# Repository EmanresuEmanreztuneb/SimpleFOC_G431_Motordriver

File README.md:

# SimpleFOC_G431_Motordriver (24V version)
A motordriver based in STM's G431 Drone ESC

Reason to create it was mainly because of the poor thermal performance of the original development board.
Now the whole "layer sandwich" is gone and every existing active layer can breath fresh air.

Changes:

<ins>**Two layer**</ins> <br>
&nbsp;&nbsp;&nbsp;&nbsp;&nbsp;&nbsp;&nbsp;&nbsp;As mentioned, the layer count has been reduced from eight to just two.<br>
&nbsp;&nbsp;&nbsp;&nbsp;&nbsp;&nbsp;&nbsp;&nbsp;The KiCad files still include two "blind" internal layers between top<br>
&nbsp;&nbsp;&nbsp;&nbsp;&nbsp;&nbsp;&nbsp;&nbsp;and bottom to test whether additional shielding makes a difference.<br>
&nbsp;&nbsp;&nbsp;&nbsp;&nbsp;&nbsp;&nbsp;&nbsp;to test if the additional shielding makes any difference.<br>
&nbsp;&nbsp;&nbsp;&nbsp;&nbsp;&nbsp;&nbsp;&nbsp;Spoiler: It doesn’t...<br>
&nbsp;&nbsp;&nbsp;&nbsp;&nbsp;&nbsp;&nbsp;&nbsp;You can remove these layers if you plan to etch the PCB at home.<br> 
&nbsp;&nbsp;&nbsp;&nbsp;&nbsp;&nbsp;&nbsp;&nbsp;However, since the price at JLC remains nearly the same, I left them in.<br>
&nbsp;&nbsp;&nbsp;&nbsp;&nbsp;&nbsp;&nbsp;&nbsp;Adding them later would be more effort than simply removing them now.<br>

<ins>**Pins**</ins> <br>
&nbsp;&nbsp;&nbsp;&nbsp;&nbsp;&nbsp;&nbsp;&nbsp;To maintain the required dimensions while sticking to a two-layer design,<br>
&nbsp;&nbsp;&nbsp;&nbsp;&nbsp;&nbsp;&nbsp;&nbsp;I unfortunately had to remove the thermal sensor and LEDs.<br>
&nbsp;&nbsp;&nbsp;&nbsp;&nbsp;&nbsp;&nbsp;&nbsp;But you get new pins for your own modifications. (PA15, C10, C11, B5)<br>

<ins>**Stable 24V**</ins> <br>
&nbsp;&nbsp;&nbsp;&nbsp;&nbsp;&nbsp;&nbsp;&nbsp;On the original version, 24V operation was borderline and carried a high<br>
&nbsp;&nbsp;&nbsp;&nbsp;&nbsp;&nbsp;&nbsp;&nbsp;risk of component failure.<br>
&nbsp;&nbsp;&nbsp;&nbsp;&nbsp;&nbsp;&nbsp;&nbsp;The current design uses the LMR23630 for the first stage (VCC to 10V),<br>
&nbsp;&nbsp;&nbsp;&nbsp;&nbsp;&nbsp;&nbsp;&nbsp;which safely handles up to 36V.<br>
&nbsp;&nbsp;&nbsp;&nbsp;&nbsp;&nbsp;&nbsp;&nbsp;A 60V version is also planned; this will require upgrading to an LMR51635<br>
&nbsp;&nbsp;&nbsp;&nbsp;&nbsp;&nbsp;&nbsp;&nbsp;and adjusting the VCC sense resistors.<br>

<ins>**BOOT / Encoder**</ins> <br>
&nbsp;&nbsp;&nbsp;&nbsp;&nbsp;&nbsp;&nbsp;&nbsp;In the previous version, the BOOT pin (PB8) was used for Encoder Z with a<br>
&nbsp;&nbsp;&nbsp;&nbsp;&nbsp;&nbsp;&nbsp;&nbsp;pull-up and capacitor. This could cause startup issues, as the system <br>
&nbsp;&nbsp;&nbsp;&nbsp;&nbsp;&nbsp;&nbsp;&nbsp;relies on the capacitor's charging time to keep PB8 low during boot.<br>

&nbsp;&nbsp;&nbsp;&nbsp;&nbsp;&nbsp;&nbsp;&nbsp;The new design uses pull-downs without capacitors. This drops support for <br>
&nbsp;&nbsp;&nbsp;&nbsp;&nbsp;&nbsp;&nbsp;&nbsp;open-collector encoders, but standard models (AMS, CUI, MT6835, MT6701) <br>
&nbsp;&nbsp;&nbsp;&nbsp;&nbsp;&nbsp;&nbsp;&nbsp;work flawlessly.<br>

<ins>**ToDo**</ins> <br>
&nbsp;&nbsp;&nbsp;&nbsp;&nbsp;&nbsp;&nbsp;&nbsp;Current-sense gain requires a surprisingly high value to match real-world<br>
&nbsp;&nbsp;&nbsp;&nbsp;&nbsp;&nbsp;&nbsp;&nbsp;measurements. ->>> Investigating the root cause.<br>

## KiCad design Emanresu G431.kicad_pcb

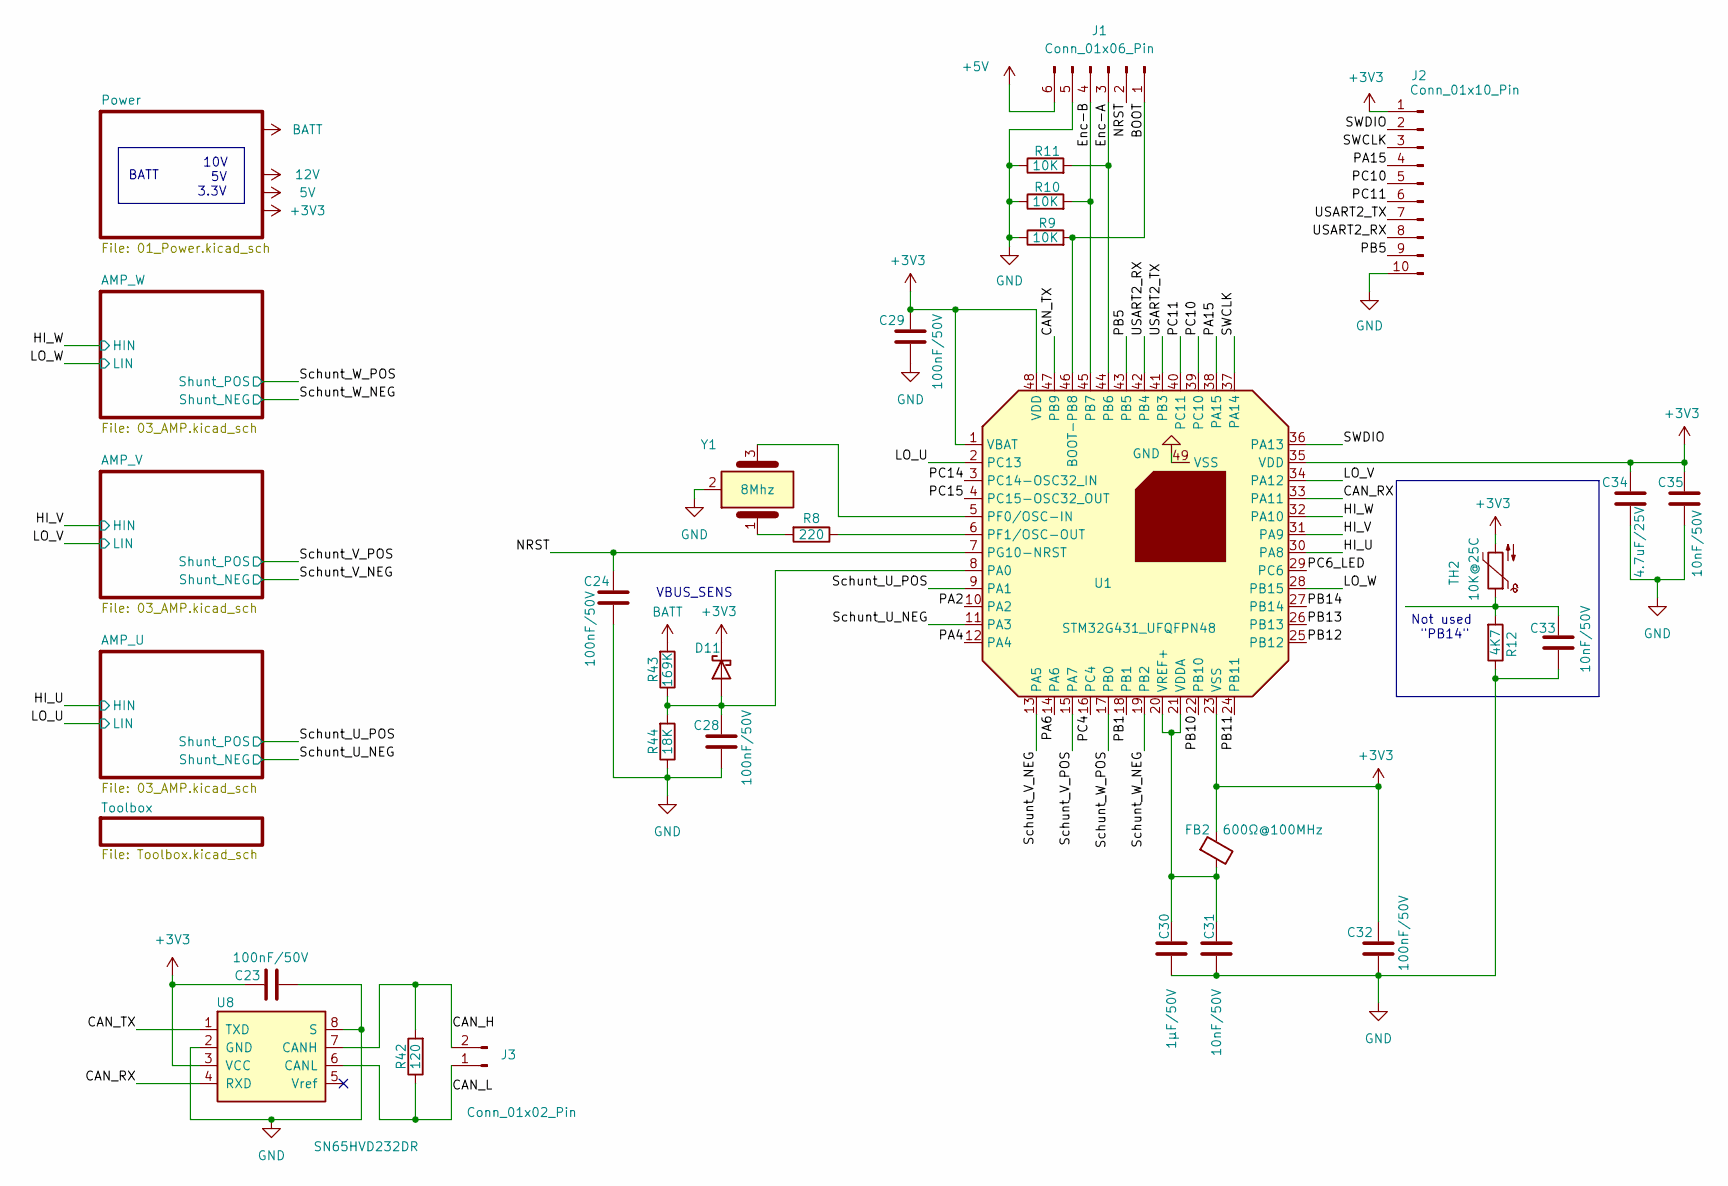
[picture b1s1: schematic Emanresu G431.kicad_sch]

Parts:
C23, C24, C28, C29, C32: 100nF/50V; C_0603_1608Metric; LCSC C14663
C30: 1μF/50V; C_0603_1608Metric; LCSC C15849
C31, C33, C35: 10nF/50V; C_0603_1608Metric; LCSC C100042
C34: 4.7uF/25V; C_0603_1608Metric; LCSC C69335
D11: D_Schottky; D_SOD-523; LCSC C2926449
FB2: 600Ω@100MHz; R_0603_1608Metric; LCSC C1002
J1: Conn_01x06_Pin; PinHeader_2x03_P2.54mm_Vertical
J2: Conn_01x10_Pin; PinHeader_1x10_P2.54mm_Vertical
J3: Conn_01x02_Pin; PinHeader_1x02_P2.54mm_Vertical
R8: 220; R_0603_1608Metric; LCSC C22962
R9, R10, R11: 10K; R_0603_1608Metric; LCSC C25804
R12: 4K7; R_0603_1608Metric; JLCPCB C23162
R42: 120; R_0603_1608Metric; LCSC C22787
R43: 169K; R_0603_1608Metric; LCSC C22817
R44: 18K; R_0603_1608Metric; LCSC C25810
TH2: 10K@25C; R_0603_1608Metric; JLCPCB C13564
U1: STM32G431_UFQFPN48; STM32 G431 QFN-48-1EP_7x7mm; LCSC C529356
U8: SN65HVD232DR; SOIC-8_3.9x4.9mm_P1.27mm; LCSC C30530
Y1: 8Mhz; CSTNE8M00GH5C000R0; LCSC C341525

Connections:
+3V3: C23.2, C29.2, C32.2, C34.2, C35.2, D11.1 (K), FB2.1, J2.1, TH2.2, U1.1 (VBAT), U1.23 (VSS), U1.35 (VDD), U1.48 (VDD), U8.3 (VCC); also elsewhere on the board
+5V: J1.6; also elsewhere on the board
/BOOT: J1.1, R9.2, U1.46 (BOOT-PB8)
/CAN_H: J3.2, R42.2, U8.7 (CANH)
/CAN_L: J3.1, R42.1, U8.6 (CANL)
/CAN_RX: U1.33 (PA11), U8.4 (RXD)
/CAN_TX: U1.47 (PB9), U8.1 (TXD)
/Enc-A: J1.3, R11.2, U1.44 (PB6)
/Enc-B: J1.4, R10.2, U1.45 (PB7)
/HI_U: U1.30 (PA8); also elsewhere on the board
/HI_V: U1.31 (PA9); also elsewhere on the board
/HI_W: U1.32 (PA10); also elsewhere on the board
/LO_U: U1.2 (PC13); also elsewhere on the board
/LO_V: U1.34 (PA12); also elsewhere on the board
/LO_W: U1.28 (PB15); also elsewhere on the board
/NRST: C24.2, J1.2, U1.7 (PG10-NRST)
/PA2: U1.10 (PA2)
/PA4: U1.12 (PA4)
/PA6: U1.14 (PA6)
/PA15: J2.4, U1.38 (PA15)
/PB1: U1.18 (PB1)
/PB5: J2.9, U1.43 (PB5)
/PB10: U1.22 (PB10)
/PB11: U1.24 (PB11)
/PB12: U1.25 (PB12)
/PB13: U1.26 (PB13)
/PB14: U1.27 (PB14)
/PC4: U1.16 (PC4)
/PC6_LED: U1.29 (PC6)
/PC10: J2.5, U1.39 (PC10)
/PC11: J2.6, U1.40 (PC11)
/PC14: U1.3 (PC14-OSC32_IN)
/PC15: U1.4 (PC15-OSC32_OUT)
/SWCLK: J2.3, U1.37 (PA14)
/SWDIO: J2.2, U1.36 (PA13)
/Schunt_U_NEG: U1.11 (PA3); also elsewhere on the board
/Schunt_U_POS: U1.9 (PA1); also elsewhere on the board
/Schunt_V_NEG: U1.13 (PA5); also elsewhere on the board
/Schunt_V_POS: U1.15 (PA7); also elsewhere on the board
/Schunt_W_NEG: U1.19 (PB2); also elsewhere on the board
/Schunt_W_POS: U1.17 (PB0); also elsewhere on the board
/USART2_RX: J2.8, U1.42 (PB4)
/USART2_TX: J2.7, U1.41 (PB3)
BATT: R43.2; also elsewhere on the board
GND: C23.1, C24.1, C28.1, C29.1, C30.1, C31.1, C32.1, C33.1, C34.1, C35.1, J1.5, J2.10, R9.1, R10.1, R11.1, R12.1, R44.1, U1.49 (VSS), U8.2 (GND), U8.8 (S), Y1.2; also elsewhere on the board
unnamed: C33.2, R12.2, TH2.1
unnamed: C28.2, D11.2 (A), R43.1, R44.2, U1.8 (PA0)
unnamed: R8.2, Y1.1
unnamed: U1.5 (PF0/OSC-IN), Y1.3
unnamed: R8.1, U1.6 (PF1/OSC-OUT)
unnamed: C30.2, C31.2, FB2.2, U1.20 (VREF+), U1.21 (VDDA)

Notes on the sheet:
10V 5V 3.3V
BATT
Not used "PB14"
VBUS_SENS

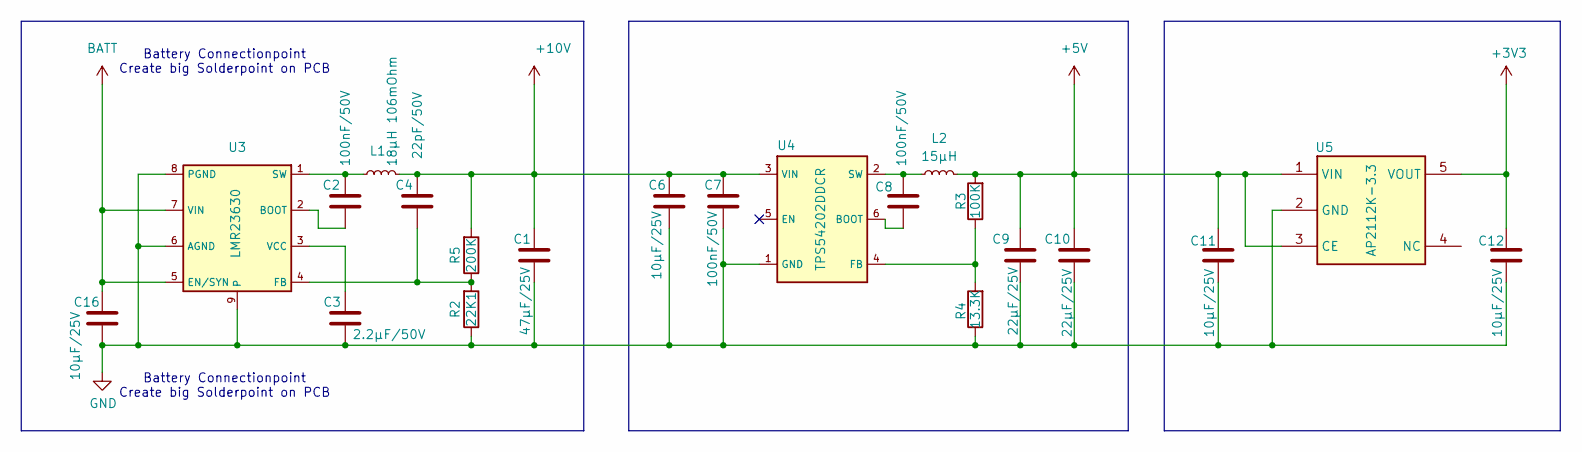
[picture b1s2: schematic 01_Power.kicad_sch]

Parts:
C1: 47μF/25V; C_1206_3216Metric; LCSC C76659
C2, C7, C8: 100nF/50V; C_0603_1608Metric; LCSC C14663
C3: 2.2μF/50V; C_1206_3216Metric; Part Number CL31B225KBHVPNE; Digikey 1276-6735-1-ND
C4: 22pF/50V; C_0805_2012Metric; LCSC C105623
C6, C16: 10μF/25V; C_0805_2012Metric; LCSC C15850
C9, C10: 22μF/25V; C_0805_2012Metric; LCSC C45783
C11, C12: 10μF/25V; C_1206_3216Metric; LCSC C13585
L1: 18µH 106mOhm; INDUCTOR-SMD_L6.0-W6.0; LCSC C467143
L2: 15µH; INDUCTOR-SMD_L4.0-W4.0; LCSC C340394
R2: 22K1; R_0603_1608Metric; LCSC C137768
R3: 100K; R_0603_1608Metric; LCSC C25803
R4: 13.3K; R_0603_1608Metric; LCSC C25952
R5: 200K; R_0603_1608Metric; LCSC C25811
U3: LMR23630; SOIC-8-1EP_3.9x4.9mm_P1.27mm_EP2.29x3mm; LCSC C601653
U4: TPS54202DDCR; SOT-23-6; LCSC C191884
U5: AP2112K-3.3; SOT-23-5; LCSC C51118

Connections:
+3V3: C12.1, U5.5 (VOUT); also elsewhere on the board
+5V: C9.1, C10.1, C11.1, L2.2, R3.2, U5.1 (VIN), U5.3 (CE); also elsewhere on the board
+10V: C1.1, C4.1, C6.1, C7.1, L1.1, R5.2, U4.3 (VIN); also elsewhere on the board
BATT: C16.2, U3.5 (EN/SYN), U3.7 (VIN); also elsewhere on the board
GND: C1.2, C3.2, C6.2, C7.2, C9.2, C10.2, C11.2, C12.2, C16.1, R2.1, R4.1, U3.6 (AGND), U3.8 (PGND), U3.9, U4.1 (GND), U5.2 (GND); also elsewhere on the board
unnamed: C2.1, U3.2 (BOOT)
unnamed: C4.2, R2.2, R5.1, U3.4 (FB)
unnamed: C2.2, L1.2, U3.1 (SW)
unnamed: C3.1, U3.3 (VCC)
unnamed: C8.2, U4.6 (BOOT)
unnamed: R3.1, R4.2, U4.4 (FB)
unnamed: C8.1, L2.1, U4.2 (SW)

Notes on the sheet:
Battery Connectionpoint Create big Solderpoint on PCB

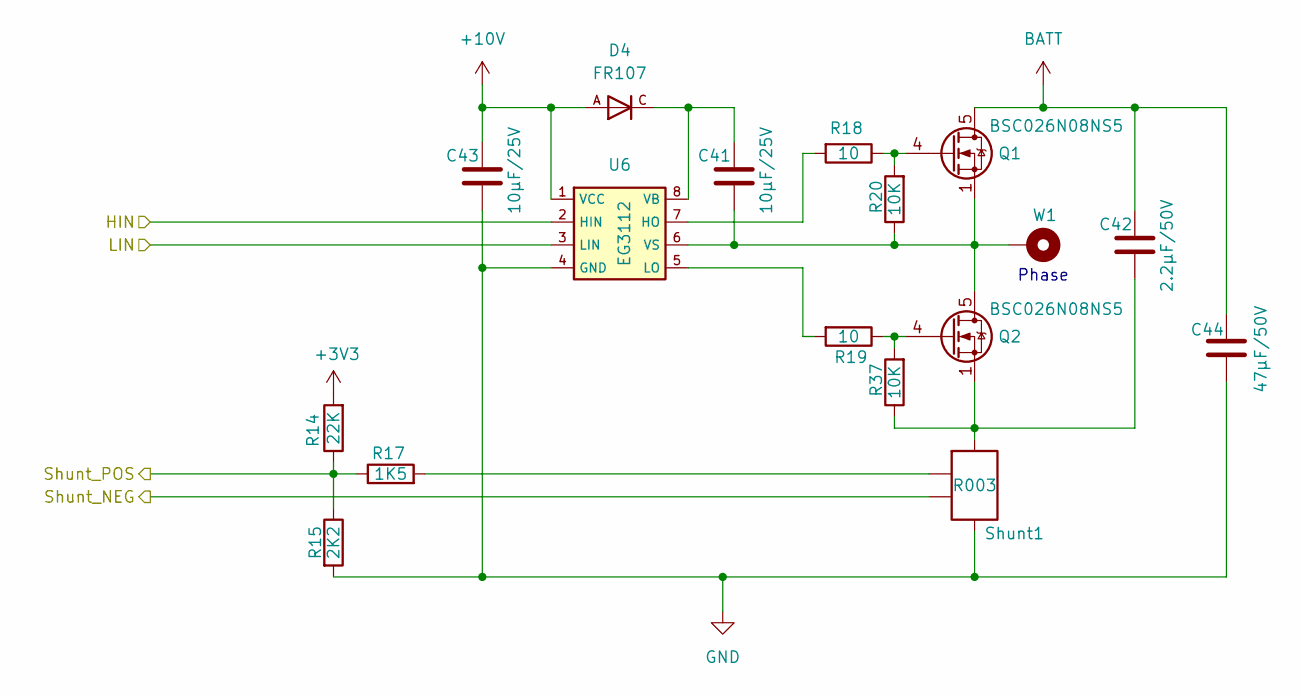
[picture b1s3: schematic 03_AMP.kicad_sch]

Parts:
C41, C43: 10μF/25V; C_0805_2012Metric; LCSC C15850
C42: 2.2μF/50V; C_1206_3216Metric; LCSC C50254
C44: 47μF/50V; CP_Radial_D6.3mm_P2.50mm; LCSC C45100
D4: FR107; FR107_SOD-123_L2.8-W1.8-LS3.7-RD-3; LCSC C3018495
Q1, Q2: BSC026N08NS5; TDSON-8-1; LCSC C5955453
R14: 22K; R_0603_1608Metric; LCSC C31850
R15: 2K2; R_0603_1608Metric; LCSC C4190
R17: 1K5; R_0603_1608Metric; LCSC C2907083
R18, R19: 10; R_0603_1608Metric; LCSC C22859
R20, R37: 10K; R_0603_1608Metric; LCSC C25804
Shunt1: R003; R_Shunt_WSK2512_6332Metric_T1.19mm; LCSC C5375459
U6: EG3112; EG3112_IRS; LCSC C111908
W1: 2.2mm_Through_Connector

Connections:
+3V3: R14.2; also elsewhere on the board
+10V: C43.2, D4.A, U6.1 (VCC); also elsewhere on the board
/HI_W: U6.2 (HIN); also elsewhere on the board
/LO_W: U6.3 (LIN); also elsewhere on the board
/Schunt_W_NEG: Shunt1.2; also elsewhere on the board
/Schunt_W_POS: R14.1, R15.1, R17.1; also elsewhere on the board
BATT: C42.1, C44.1, Q1.5 (D); also elsewhere on the board
GND: C43.1, C44.2, R15.2, Shunt1.1, U6.4 (GND); also elsewhere on the board
unnamed: C42.2, Q2.1 (S), Q2.2 (S), Q2.3 (S), R37.1, Shunt1.4
unnamed: Q1.4 (G), R18.1, R20.2
unnamed: C41.1, Q1.1 (S), Q1.2 (S), Q1.3 (S), Q2.5 (D), R20.1, U6.6 (VS), W1.1
unnamed: Q2.4 (G), R19.1, R37.2
unnamed: R17.2, Shunt1.3
unnamed: R18.2, U6.7 (HO)
unnamed: R19.2, U6.5 (LO)
unnamed: C41.2, D4.C, U6.8 (VB)

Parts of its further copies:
C14, C19, C45, C46: 10μF/25V; C_0805_2012Metric; LCSC C15850
C15, C20: 2.2μF/50V; C_1206_3216Metric; LCSC C50254
C17, C22: 47μF/50V; CP_Radial_D6.3mm_P2.50mm; LCSC C45100
D7, D10: FR107; FR107_SOD-123_L2.8-W1.8-LS3.7-RD-3; LCSC C3018495
Q3, Q4, Q5, Q6: BSC026N08NS5; TDSON-8-1; LCSC C5955453
R21, R31: 22K; R_0603_1608Metric; LCSC C31850
R22, R32: 2K2; R_0603_1608Metric; LCSC C4190
R24, R34: 1K5; R_0603_1608Metric; LCSC C2907083
R25, R26, R35, R36: 10; R_0603_1608Metric; LCSC C22859
R27, R28, R39, R40: 10K; R_0603_1608Metric; LCSC C25804
Shunt2, Shunt3: R003; R_Shunt_WSK2512_6332Metric_T1.19mm; LCSC C5375459
U2: 2.2mm_Through_Connector
U9, U11: EG3112; EG3112_IRS; LCSC C111908
V1: 2.2mm_Through_Connector

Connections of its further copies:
+3V3: R21.2, R31.2; also elsewhere on the board
+10V: C45.2, C46.2, D7.A, D10.A, U9.1 (VCC), U11.1 (VCC); also elsewhere on the board
/HI_U: U11.2 (HIN); also elsewhere on the board
/HI_V: U9.2 (HIN); also elsewhere on the board
/LO_U: U11.3 (LIN); also elsewhere on the board
/LO_V: U9.3 (LIN); also elsewhere on the board
/Schunt_U_NEG: Shunt3.2; also elsewhere on the board
/Schunt_U_POS: R31.1, R32.1, R34.1; also elsewhere on the board
/Schunt_V_NEG: Shunt2.2; also elsewhere on the board
/Schunt_V_POS: R21.1, R22.1, R24.1; also elsewhere on the board
BATT: C15.1, C17.1, C20.1, C22.1, Q3.5 (D), Q5.5 (D); also elsewhere on the board
GND: C17.2, C22.2, C45.1, C46.1, R22.2, R32.2, Shunt2.1, Shunt3.1, U9.4 (GND), U11.4 (GND); also elsewhere on the board
unnamed: C15.2, Q4.1 (S), Q4.2 (S), Q4.3 (S), R28.1, Shunt2.4
unnamed: C20.2, Q6.1 (S), Q6.2 (S), Q6.3 (S), R40.1, Shunt3.4
unnamed: Q3.4 (G), R25.1, R27.2
unnamed: C14.1, Q3.1 (S), Q3.2 (S), Q3.3 (S), Q4.5 (D), R27.1, U9.6 (VS), V1.1
unnamed: Q4.4 (G), R26.1, R28.2
unnamed: Q5.4 (G), R35.1, R39.2
unnamed: C19.1, Q5.1 (S), Q5.2 (S), Q5.3 (S), Q6.5 (D), R39.1, U2.1, U11.6 (VS)
unnamed: Q6.4 (G), R36.1, R40.2
unnamed: R24.2, Shunt2.3
unnamed: R34.2, Shunt3.3
unnamed: R25.2, U9.7 (HO)
unnamed: R26.2, U9.5 (LO)
unnamed: C14.2, D7.C, U9.8 (VB)
unnamed: R35.2, U11.7 (HO)
unnamed: R36.2, U11.5 (LO)
unnamed: C19.2, D10.C, U11.8 (VB)

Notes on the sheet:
Phase

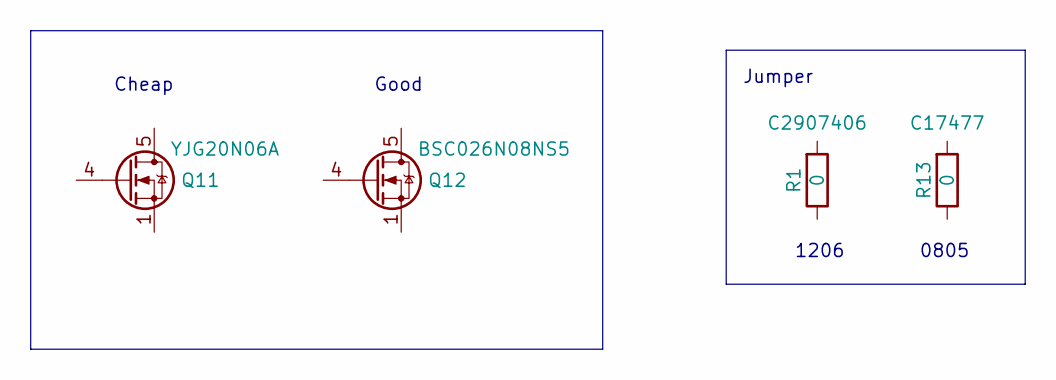
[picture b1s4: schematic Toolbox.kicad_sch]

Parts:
Q11: YJG20N06A; TDSON-8-1; JLC C919592
Q12: BSC026N08NS5; TDSON-8-1; JLC C5955453
R1: 0; R_1206_3216Metric; JLCPCB C2907406
R13: 0; R_0805_2012Metric; JLCPCB C17477

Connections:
unnamed: Q11.1 (S), Q11.2 (S), Q11.3 (S)
unnamed: Q12.1 (S), Q12.2 (S), Q12.3 (S)

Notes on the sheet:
1206
Good
Jumper
0805
Cheap

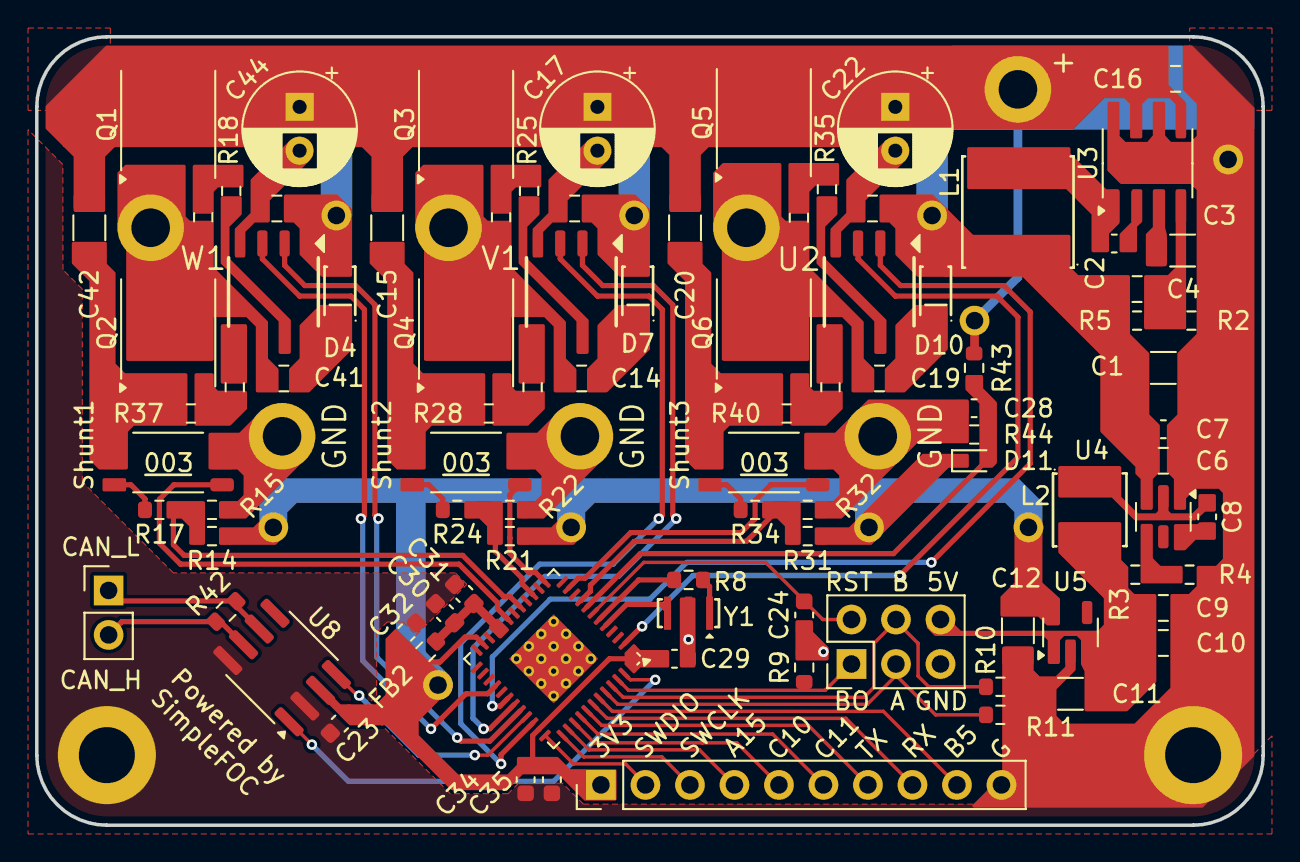
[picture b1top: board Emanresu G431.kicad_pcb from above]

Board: 4 copper layers, 70.0 x 45.0 mm, 110 parts (0 on the bottom side), 69 nets.

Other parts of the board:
3V3, 3V3#2, 3V3#3, 3V3#4, 3V3#5, 10V, 10V#2, 10V#3: Single_Header_P2.54mm_Round
+: Val**; 2.2mm_Through_Connector
BATT: Single_Header_P2.54mm_Round
GND: Val**; 2.2mm_Through_Connector
GND#2, GND#3: Val**; 2.2mm_Through_Connector
J?: Single_Header_P2.54mm_Round

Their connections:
+3V3: 3V3.1, 3V3#2.1, 3V3#3.1, 3V3#4.1, 3V3#5.1; also elsewhere on the board
+10V: 10V.1, 10V#2.1, 10V#3.1; also elsewhere on the board
BATT: +.1, BATT.1; also elsewhere on the board
GND: GND.1, GND#2.1, GND#3.1, J?.1; also elsewhere on the board

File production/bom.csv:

Designator,Footprint,Quantity,Value,LCSC Part #
C1,1206,1,47μF/25V,C76659
"C10, C9",0805,2,22μF/25V,C45783
"C11, C12",1206,2,10μF/25V,C13585
"C14, C16, C19, C41, C43, C45, C46, C6",0805,8,10μF/25V,C15850
"C15, C20, C3, C42",1206,4,2.2μF/50V,C50254
"C17, C22, C44",CP_Radial_D6.3mm_P2.50mm,3,47μF/50V,C45100
"C2, C23, C24, C28, C29, C32, C7, C8",0603,8,100nF/50V,C14663
C30,0603,1,1μF/50V,C15849
"C31, C35",0603,2,10nF/50V,C100042
C34,0603,1,4.7uF/25V,C69335
C4,0805,1,22pF/50V,C105623
"D10, D4, D7",FR107_SOD-123_L2.8-W1.8-LS3.7-RD-3,3,FR107,C3018495
D11,D_SOD-523,1,D_Schottky,C2926449
FB2,0603,1,600Ω@100MHz,C1002
L1,INDUCTOR-SMD_L6.0-W6.0,1,18µH 106mOhm,C467143
L2,INDUCTOR-SMD_L4.0-W4.0,1,15µH,C340394
"Q1, Q2, Q3, Q4, Q5, Q6",TDSON-8-1,6,BSC026N08NS5,C5955453
"R10, R11, R20, R27, R28, R37, R39, R40, R9",0603,9,10K,C25804
"R14, R21, R31",0603,3,22K,C31850
"R15, R22, R32",0603,3,2K2,C4190
"R17, R24, R34",0603,3,1K5,C2907083
"R18, R19, R25, R26, R35, R36",0603,6,10,C22859
R2,0603,1,22K1,C137768
R3,0603,1,100K,C25803
R4,0603,1,13.3K,C25952
R42,0603,1,120,C22787
R43,0603,1,169K,C22817
R44,0603,1,18K,C25810
R5,0603,1,200K,C25811
R8,0603,1,220,C22962
"SHUNT1, SHUNT2, SHUNT3",R_Shunt_WSK2512_6332Metric_T1.19mm,3,R003,C5375459
U1,STM32 G431 QFN-48-1EP_7x7mm,1,STM32G431_UFQFPN48,C529356
"U11, U6, U9",EG3112_IRS,3,EG3112,C111908
U3,SOIC-8-1EP_3.9x4.9mm_P1.27mm_EP2.29x3mm,1,LMR23630,C601653
U4,SOT-23-6,1,TPS54202DDCR,C191884
U5,SOT-23-5,1,AP2112K-3.3,C51118
U8,SOIC-8_3.9x4.9mm_P1.27mm,1,SN65HVD232DR,C30530
Y1,CSTNE8M00GH5C000R0,1,8Mhz,C341525
